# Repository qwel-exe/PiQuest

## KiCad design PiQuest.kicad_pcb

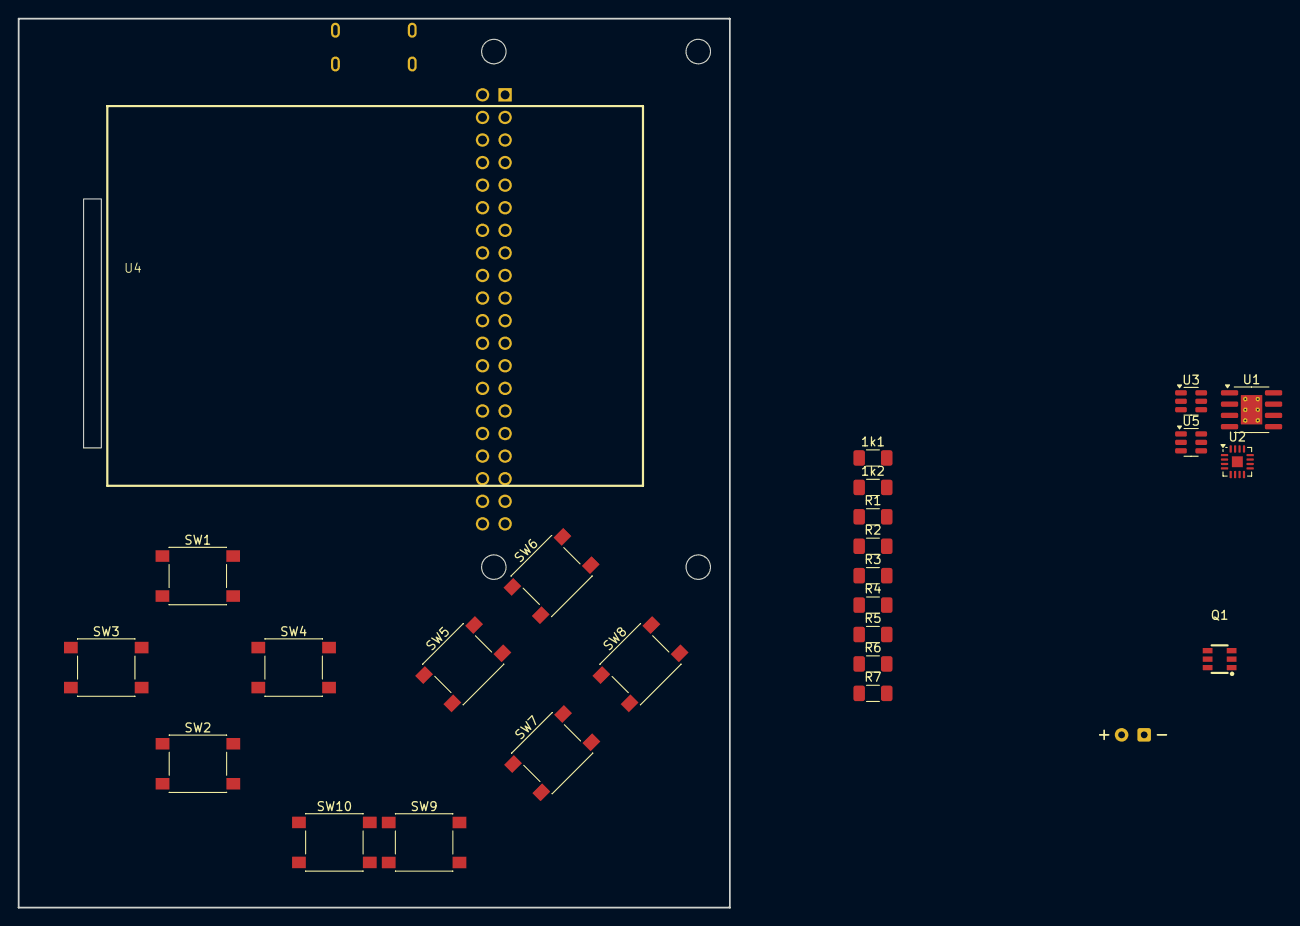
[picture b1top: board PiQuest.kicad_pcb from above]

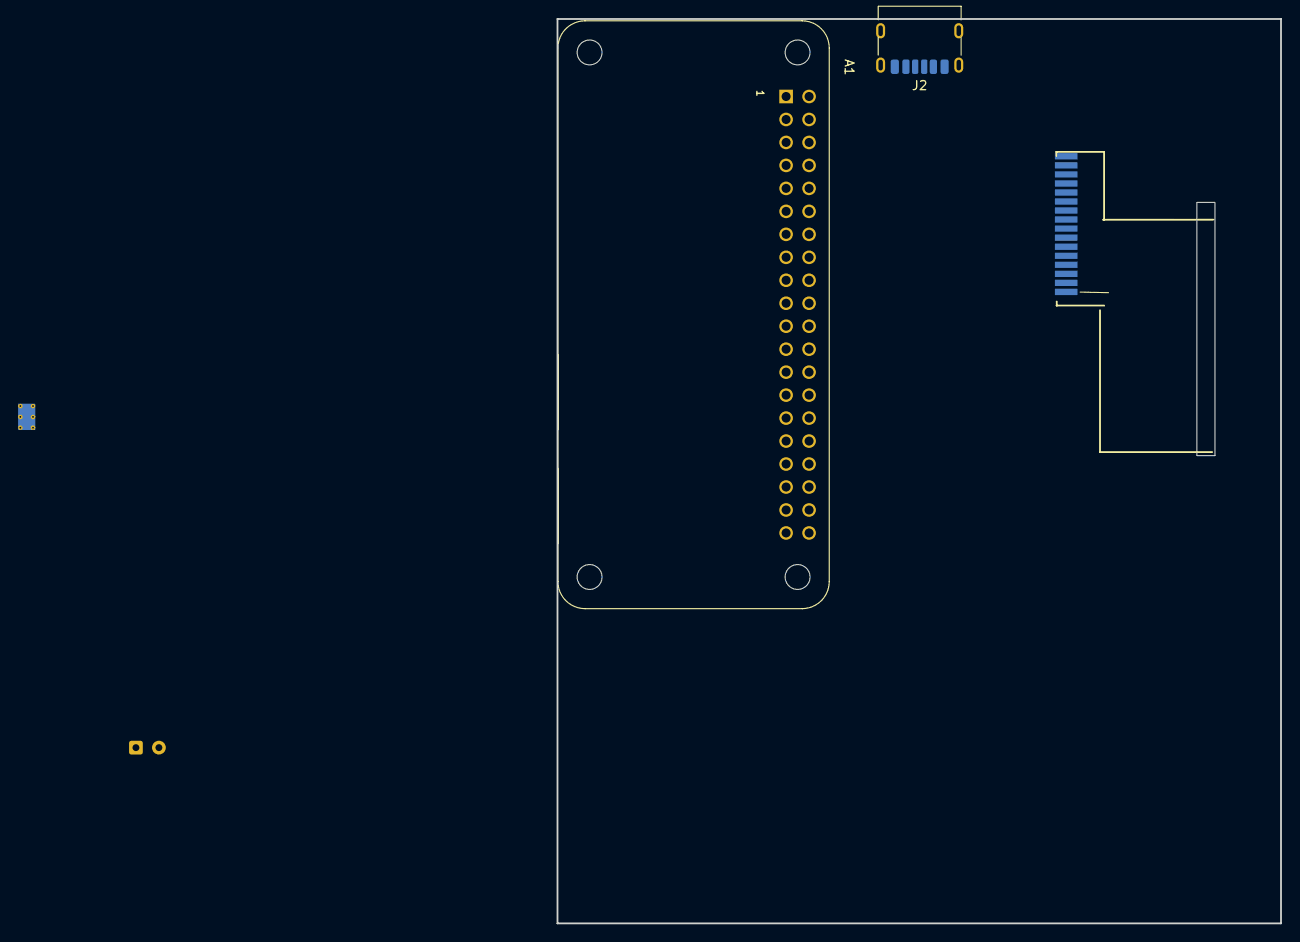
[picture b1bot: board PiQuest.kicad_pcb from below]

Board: 2 copper layers, 80.0 x 100.0 mm, 28 parts (2 on the bottom side), 25 nets, no tracks yet.

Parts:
1k1, 1k2: R; R_1206_3216Metric_Pad1.30x1.75mm_HandSolder
A1: RASPBERRYPI-ZERO; RASPBERRYPI-ZERO_RPI-ZERO
BT1: Battery_Cell; Battery
J2: USB_C_Receptacle_PowerOnly_6P; USB_C_Receptacle_HRO_TYPE-C-31-M-17
Q1: FS8205A_C2830320; SOT-23-6_L2.9-W1.6-P0.95-LS2.8-BR
R1, R2: R; R_1206_3216Metric_Pad1.30x1.75mm_HandSolder
R3: 100; R_1206_3216Metric_Pad1.30x1.75mm_HandSolder
R4, R5: 2k; R_1206_3216Metric_Pad1.30x1.75mm_HandSolder
R6: 30k; R_1206_3216Metric_Pad1.30x1.75mm_HandSolder
R7: 10k; R_1206_3216Metric_Pad1.30x1.75mm_HandSolder
SW1, SW2, SW3, SW4, SW5, SW6, SW7, SW8, SW9, SW10: SW_Omron_B3FS; SW_SPST_PTS645
U1: TP4056-42-ESOP8; SOIC-8-1EP_3.9x4.9mm_P1.27mm_EP2.41x3.3mm_ThermalVias
U2: MAX98357A; TQFN-16-1EP_3x3mm_P0.5mm_EP1.23x1.23mm
U3: DW01A; SOT-23-6
U4: HS24CG003-ARX; lcd
U5: MT3608; SOT-23-6

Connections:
+3.3V: A1.1 (3V3[1]), U4.8 (VCC)
+5V: A1.2 (5V[1]), R6.1
BCLK: A1.12 (GPIO18), U2.16 (BCLK)
BN: A1.9 (GND[1]), BT1.2 (-), J2.A12 (GND), J2.B12 (GND), J2.S1 (SHIELD), R1.2, R2.2, R4.1, R5.1, R7.2, SW1.2, SW2.1, SW3.1, SW4.2, SW5.1, SW6.2, SW7.1, SW8.2, SW9.2, SW10.1, U1.1 (TEMP), U1.3 (GND), U2.3 (GND), U2.11 (GND), U2.15 (GND), U3.6 (GND), U4.1 (GND), U5.2 (GND)
BP: BT1.1 (+), Q1.1 (S1), Q1.3 (S2), R3.1, U1.5 (BAT)
CS: A1.24 (~CE0/GPIO8), U4.12 (CS)
DC: A1.22 (GEN/6GPIO25), U4.10 (DC)
DIN: A1.38 (GPIO20), U2.1 (DIN)
LRCLK: A1.35 (GPIO19), U2.14 (LRCLK)
unnamed: J2.A5 (CC1), R1.1
unnamed: J2.B5 (CC2), R2.1
unnamed: Q1.6 (G1), U3.3 (OC)
unnamed: Q1.4 (G2), U3.1 (OD)
unnamed: U5.4 (EN), U5.5 (IN)
unnamed: R4.2, U1.2 (PROG)
unnamed: 1k1.2, U1.7 (~CHRG)
unnamed: 1k2.2, U1.6 (~STDBY)
unnamed: U2.7 (VDD), U2.8 (VDD)
unnamed: R5.2, U3.2 (CS)
unnamed: R3.2, U3.5 (VCC)
unnamed: R6.2, R7.1, U5.3 (FB)
RST: A1.13 (GPIO27/GEN2), U4.13 (RST)
SCL: A1.23 (GPIO11/SCLK), U4.11 (SCL)
SDI: A1.19 (GPIO10/MOSI), U4.9 (SDI)
VBUS: J2.A9 (VBUS), J2.B9 (VBUS), U1.4 (V_{CC}), U1.8 (CE)

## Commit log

2025-05-16 Initial commit for PiQuest
2025-05-18 added buttons
2025-05-18 fixed lcd footprint
2025-05-18 fixed display
2025-05-19 added usb c and fixed alignment issues
2025-05-20 better schematics
